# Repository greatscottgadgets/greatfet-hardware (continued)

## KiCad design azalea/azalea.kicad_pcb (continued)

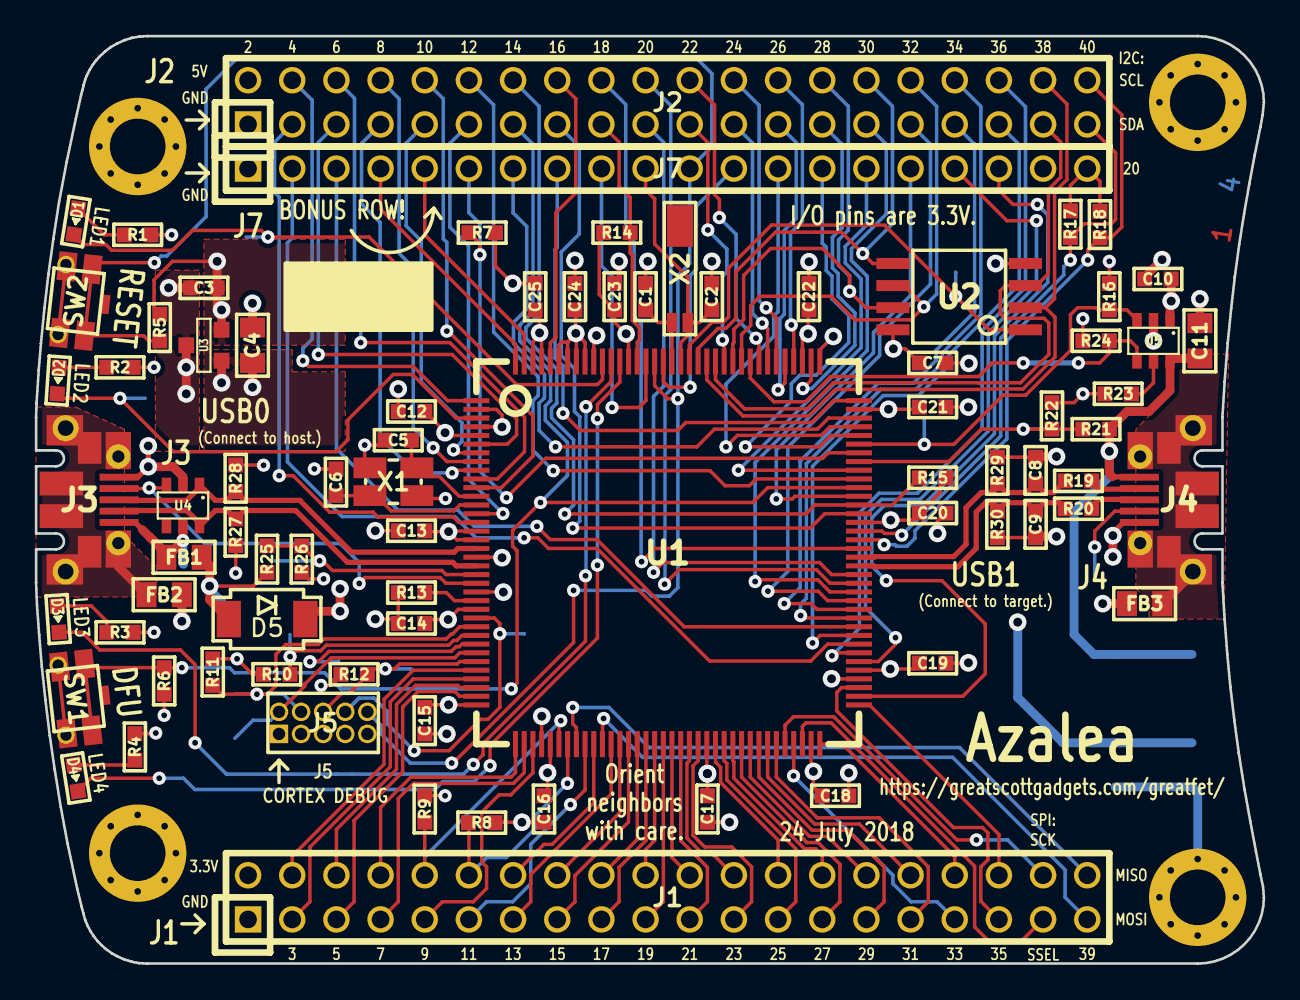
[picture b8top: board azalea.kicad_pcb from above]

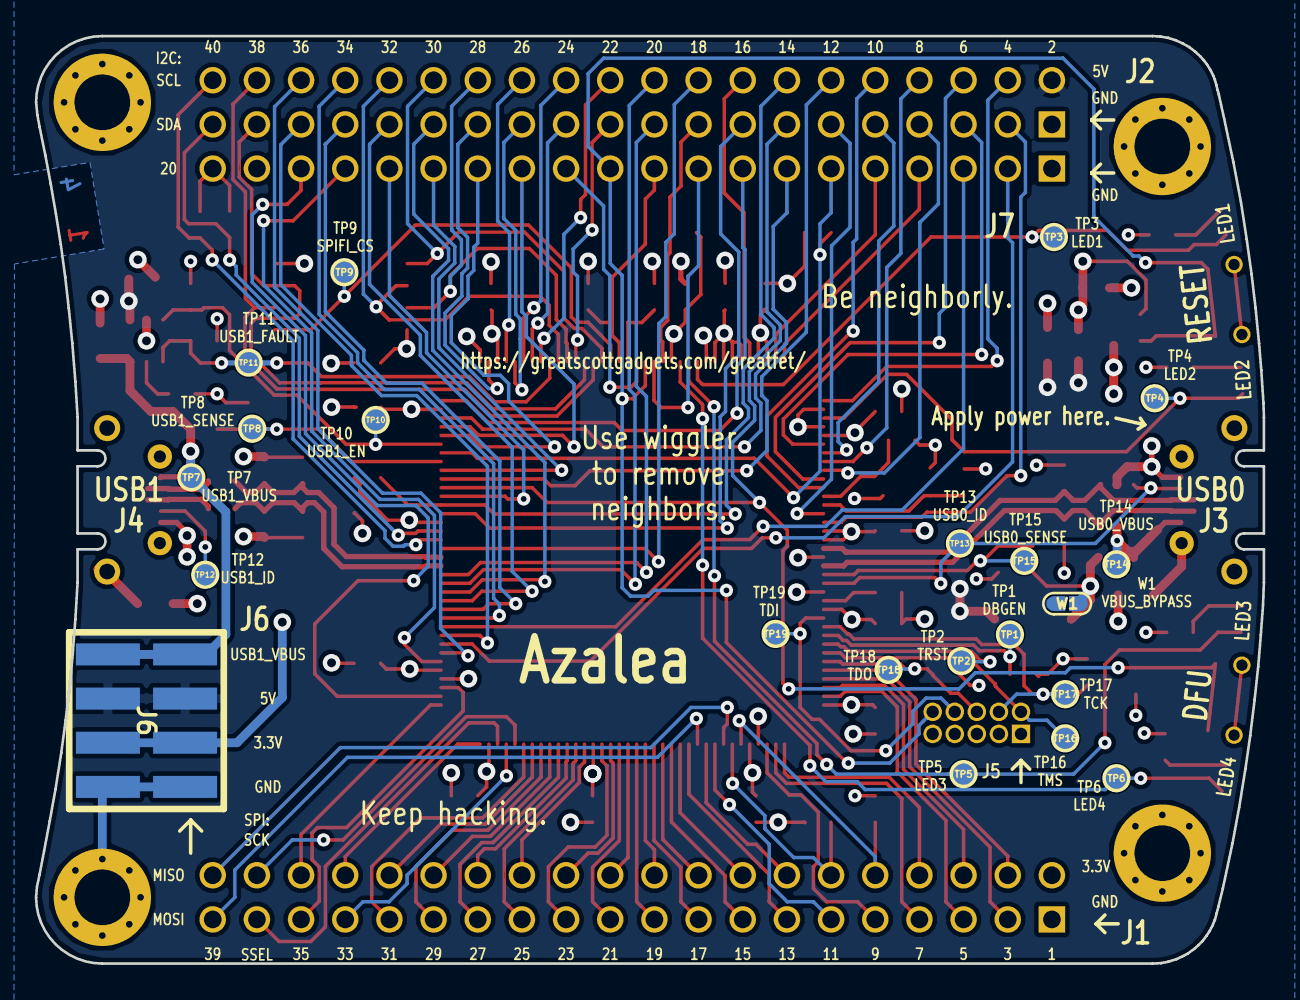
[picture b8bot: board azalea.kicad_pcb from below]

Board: 4 copper layers, 70.6 x 53.3 mm, 103 parts (21 on the bottom side), 133 nets.

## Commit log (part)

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2015-08-29 gsg-kicad-lib submodule
2015-08-29 started azalea, a prototype GreatFET main board
2015-08-29 lazy markdown workaround
2015-09-01 azalea: completed most of schematic apart from the expansion interface
2015-09-01 azalea: add library cache
2015-09-15 azalea: USB1 VBUS switching
2015-09-19 azalea: I2C pull-ups, optional RTC section
2015-09-19 azalea: removed USB0_ID pull-up as there is an internal pull-up
2015-09-20 azalea: proper USB1 switching
2015-09-21 azalea: neighbor interface
2015-09-21 azalea: bonus row of pins that might get cut
2015-09-21 azalea: schematic notes
2015-09-21 azalea: renamed reference designators from P to J or TP to avoid confusion with LP4330 pin symbols
2015-09-21 azalea: annotated
2015-09-21 azalea: title and copyright on schematic
2015-09-21 azalea: renamed RTC header
2015-09-21 azalea: module assignments
2015-09-21 azalea: reversed RTC XTAL connections
2015-09-23 azalea: PCB shape
2015-09-23 azalea: made PCB slightly longer and narrower, mounting holes assymmetrical
2015-09-23 azalea: approximate component placement
2015-09-23 azalea: selected lower profile switch
2015-09-24 azalea: completed most of the routing
2015-09-24 azalea: finished first pass at routing
2015-09-24 azalea: reoriented ESD diode, added USB0_ID protection
2015-09-24 azalea: corrected DRC errors
2015-09-24 azalea: edge cutouts for USB connectors, made PCB edge continuous
2015-09-24 azalea: silkscreen labels
2015-09-24 azalea: added layer legend, renamed inner layers
2015-09-25 azalea: neighbor template
2015-09-25 neighbor template: removed USB connector edge cutouts
2015-09-25 begonia: a GIMME for GreatFET
2015-09-25 begonia: required silkscreen text
2015-09-25 begonia: date stamp bump
2015-09-25 Ignore autosave files generated by some versions of Kicad
2015-09-25 started crocus, an nRF24L01+ neighbor inspired by The Next Hope Badge
2015-09-27 crocus: finished layout
2015-09-27 neighbor-template: track cleanup
2015-09-27 begonia: extended spring pin PCB edge for fit into IM-Me battery compartment
2015-09-27 begonia: added alternative pins for RESET_N signal
2015-09-27 daffodil: a through-hole prototyping neighbor
2015-09-27 begonia: added back mask layer
2015-09-27 crocus: added back mask layer
2015-10-19 max current note
2015-10-20 changed 47 pF caps to 18 pF for bom reduction
2015-10-20 RTC XTAL is no longer DNP
2015-10-20 azalea: made USB connectors protrude less from PCB edge, lengthened pads to ease soldering
2015-10-20 azalea: nudged some 0402s that did not need to be so close together
2015-10-29 extended crystal pads for easier soldering
2015-10-29 crocus: switched from vertical to PCB edge RP-SMA connector
2015-10-31 azalea: corrected value of 47 pF caps that were changed to 18 pF
2015-10-31 azalea: LED part selection
2015-11-01 azalea: pin header part selection
2015-11-01 azalea: renamed MCU_XTAL
2015-11-01 neighbors: pin header part selection
2015-11-01 neighbors: alternate header selection
2015-11-01 daffodil: oops, J7 should not be DNP
2016-01-20 crocus: added part number for P1
2016-01-20 begonia: designated solder jumpers DNP
2016-01-20 begonia: designated through-hole prototype area DNP
2016-01-20 daffodil: added solderless breadboard
2016-06-29 azalea: moved layer legend
2016-06-29 azalea: pin 1 arrows
2016-07-19 renamed Azalea to GreatFET One
2016-07-19 GreatFET One: corrected directory name
2016-07-22 Foxglove: a level shifting multi-function neighbor, only does level shifting for now
2016-07-22 Edelweiss: a CC1310 wireless neighbor, incomplete
2016-08-17 Add readmes to make navigating hardware designs a little easier
2016-08-27 GreatFET One: schematic changes permitting power supplied by neighbor
    Renamed VBUS on J2 pin 2 to +5V and isolated +5V from USB0_VBUS with D5,
    a diode to protect the USB host. Renamed U1 pin 21 from VBUS to
    USB0_SENSE and added a votage divider (R25 and R26) to protect this pin
    from voltages greater than 3.6 V in the unusual situation that
    USB0_SENSE is present without VCC present. (This happened and appears
    to have resulted in damage when someone applied power to a home-built
2016-08-27 GreatFET One: 18k resistor component selection, R22 and R26
2016-08-29 GreatFET One: changed U5 from NX5P2553GVH (end of life) to AP2553W6-7, updated ILIM resistor R23
2016-08-29 GreatFET One: moved R17 and R18 out of probable lever area
2016-08-30 GreatFET One: moved test points to bottom for manufacturing
2016-08-30 GreatFET One: spread a few components apart for easier hand assembly
2016-08-30 GreatFET One: more USB0 test points
2016-08-30 GreatFET One: more JTAG test points
2016-08-30 GreatFET One: J6 POWER header on bottom, can be used with single row header on edge, could be useful for non-USB applications of U5 power switch
2016-08-30 GreatFET One: silkscreen update
2016-08-30 GreatFET One: replaced D5 with a part with lower forward voltage to maximize the usefulness of +5V for USB1 and neighbors
2016-08-30 GreatFET One: minor routing tweaks to improve +5V zone
2016-09-24 GreatFET One: corrected part numbers for 18k resistors
2016-10-17 GreatFET One: Changed resistor values to fix voltage dividers for USB0 and USB1 VBUS sensing.
2016-11-20 Crocus: Corrected I2C connection errors, thanks to docprofsky!
2016-12-05 Gladiolus: an IR neighbor, schematic mostly complete
2016-12-21 replaced LMH6629 with THS4520 for easier interface to AD8330
2016-12-22 Gladiolus: finished neighbor pin selection
2016-12-22 Gladiolus: module selection
2016-12-22 Gladiolus: reversed potentiometers
2016-12-23 Gladiolus: completed initial layout
2016-12-23 Gladiolus: added female header to block direct TX to RX light
2016-12-23 Gladiolus: length matching
2016-12-30 Crocus: updated date on silkscreen
2017-01-02 Gladiolus: corrected part selection for 0402 0 ohm resistors
2017-01-16 Gladiolus: added TX DAC, changed TX GPIO pins
2017-01-20 Gladiolus: corrected voltage range of RV2
2017-01-20 Gladiolus: added LED/photodiode expansion to P1
2017-01-26 Gladiolus: updated date on silkscreen
2017-01-28 GreatFET One: moved J5 for additional clearance needed for enclosure
2017-02-01 Restored VBUS voltage dividers which work correctly now that we learned how to turn off VBUS discharge in the microcontroller.
2017-02-13 updated from discontinued W25Q16DVSSIG to compatible W25Q16JVSSIQ
2017-02-20 Added part numbers for R57, R64, R66, R69, & R71; Changed values of R64, R66, & R69 to reflect part.
2017-03-11 Gladiolus: changed R57 from 2k to 20k to bring DAC output current into supported range
2017-03-11 Gladiolus: changed R70 and R71 values to shift common mode voltage of DAC amplifier output
2017-03-11 Gladiolus: inverted DAC output by swapping differential output pin connections
2017-07-19 GreatFET One: updated schematic symbols to newer kicad library
2017-11-10 Added jasmine neighbor
2017-11-14 Changed README.md and J3 no connect.
2017-11-15 Turned Jasmine into 2-layer board. Re-routes, fixes.
2017-11-15 Cleaned up some paths, and updated submodule.
2017-12-08 solder mask clearance settings plus some trace width changes
2017-12-14 Update LICENSE
2018-01-12 GreatFET One: added 15k pull-down resistors to USB signals to support host mode
2018-02-01 Cleaning up GF and jasmine to fix local repo
2018-03-01 GreatFET One: marked W1 test point DNP
2018-03-03 Eliminated redundant hardware directory because we decided to keep nothing but hardware in this repository.
2018-03-03 consistent spelling in README.md
2018-03-03 moved .gitignore to top level
2018-03-05 added Wiggler, a lever for separating neighbors
2018-03-07 GreatFET One: removed requirement for low insertion force headers for J1 and J2 now that we have the wiggler
2018-03-07 GreatFET One: revised component selection based on availability
2018-03-07 GreatFET One: added SMD insert attribute for all components to be installed at SMT assembly
2018-03-07 Wiggler: selected layers for plotting
2018-05-22 Fixed abs path to home directory
2018-06-04 Added Lily schematic and layout. Modified .gitmodules for gsg kicad library.
2018-06-11 Updated copper pours on Lily PCB layout, added comments on schematic.
2018-06-19 Revised Lily schematic and PCB: Added connections for threshold detection mode and improved RF impedance matching.
2018-06-28 Updated submodule
2018-06-28 Revised Lily PCB: added silkscreen labels, rerouted tracks, etc.
2018-06-29 Fixed bad track
2018-06-29 Fixed gsg-kicad-lib submodule
2018-07-02 Corrected Lily BOM
2018-07-13 Added (incomplete) Orchid schematic
2018-07-20 Working on Orchid pcb layout
2018-07-23 Completed PCB layout
2018-07-24 GreatFET One: added ADC pin straps for hardware version detection
2018-07-24 Renamed GreatFET One back to Azalea. The name GreatFET One will be used only for boards marketed by Great Scott Gadgets. Azalea should be used to refer to other boards of the same design.
2018-07-24 Azalea: updated URL on silkcreen, adding greatfet and changing the protocol to https
2018-07-24 Azalea: copied some front silkscreen to back silkscreen
2018-07-24 Azalea: nudged message on silkscreen to avoid via
2018-07-24 added Narcissus, a neighbor for testing Azalea
2018-07-24 Narcissus: corrected U4 pin 7 power supply connection
2018-07-30 Added iCE40HX4K-TQ144 symbol to gsg library
2018-08-08 Revised Lucky Bamboo schematic and PCB layout: Added LNA amplifiers on RF input stage and baluns for all RF input/output ports. Added connections from IRQ1/IRQ2 to GreatFET header. Updated GSG Kicad 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
2018-08-16 Corrected Lily BOM. Updated gsg-kicad-lib
2018-08-21 Added greenPAK and iCE40 to schematic, started routing power connections
2018-10-07 Daffodil: removed GND from J7 pin 10, updated silkscreen
2018-10-13 Azalea: changed J7 pin 10 from GND to RTCX1
2018-11-01 Added RF splitter/amp to orchid schematic
2018-11-01 renamed Orchid to Lucky Bamboo
2018-11-01 Added sym-lib-table and updated schemactic symbols
2019-01-03 Completed new amplifier/splitter section in schematic and layout.
2019-01-03 Fixed clearances and silk screen date
2019-01-11 standardize on 7-bit format for I2C address documentation
2019-01-26 minor updates to neighbor template
2019-01-26 Quince: a dual comparator neighbor for 1-bit SDR experimentation
2019-01-26 updated gsg-kicad-lib for Quince
2019-02-11 JASMINE: Revised charge rate config; Added DNP JST connector; Added DNP screw terminal; Added load switch w/ LED indicator; Updated labeling on silkscreen LUCKY BAMBOO: updated soldermask clearance
2019-03-18 Rev 2! Added 2 MUXs and an I/O expander for controlling charge rate, and reading current rates from your GreatFET. Also added a 32 MHz oscillator for eventual GreatFET sleep mode.
2019-03-19 SPI routing
2019-03-19 Added transistor notes
2019-03-19 Added AC/DC coupling switch and removed central header
2019-03-19 Added TODO design notes
2019-03-19 Added AC/DC coupling switch using 74LVC1G3157
2019-03-19 BOM: Changed SMA connectors to RP-SMA and changed SPORT header
2019-03-19 Added multiplexors to bank A
2019-03-19 Added ice40 symbol
2019-03-19 Gladiolus: Added AD/DC coupling switch, removed DNP components for inversion, added switch to fully turn off TX, routed TX LED current to ADC
2019-03-19 Minor change to Gladiolus silkscreen. Began designing Foxglove level shifters / comparators and power supplies.
2019-03-19 Lucky Bamboo: Rerouted RX RF signals and rearranged schematic to be consistent with layout. Gladiolus: Routed incomplete signal near TX transistor.
2019-03-19 updated gsg-kicad-lib
2019-03-20 Updated Daffodil silkscreen, porto area, and breadboard.
2019-03-20 Minor adjustments to silkscreen
2019-03-21 Fixed Daffodil library symbols.
2019-03-25 Removed all 'rescue' symbols
2019-03-28 Changed resistor on voltage divider MUX to 100k resistors; Added an optional voltage divider to screw terminal input
2019-03-29 Completed component and footprint selection
2019-04-03 Cleaned up jasmine.sch; Started Jasmine layout
2019-05-16 Updates to jasmine schematic and layout; Updated neighbor-template to be compatible with KiCAD 5.1.2
2019-05-21 Added a GND plain to to the top copper layer of Daffodil.
2019-05-21 Updated date on Daffodil silkscreen.
2019-05-23 Daffodil: nudged proto area to match .1 inch spacing with neighbor headers
2019-05-27 remove and ignore generated .net files
2019-05-27 replace full paths with relative paths
